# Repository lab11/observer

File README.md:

Observer
========

Observer is an indoor monitoring sensor platform that is optimized to work
with [GAP](https://github.com/lab11/gap).

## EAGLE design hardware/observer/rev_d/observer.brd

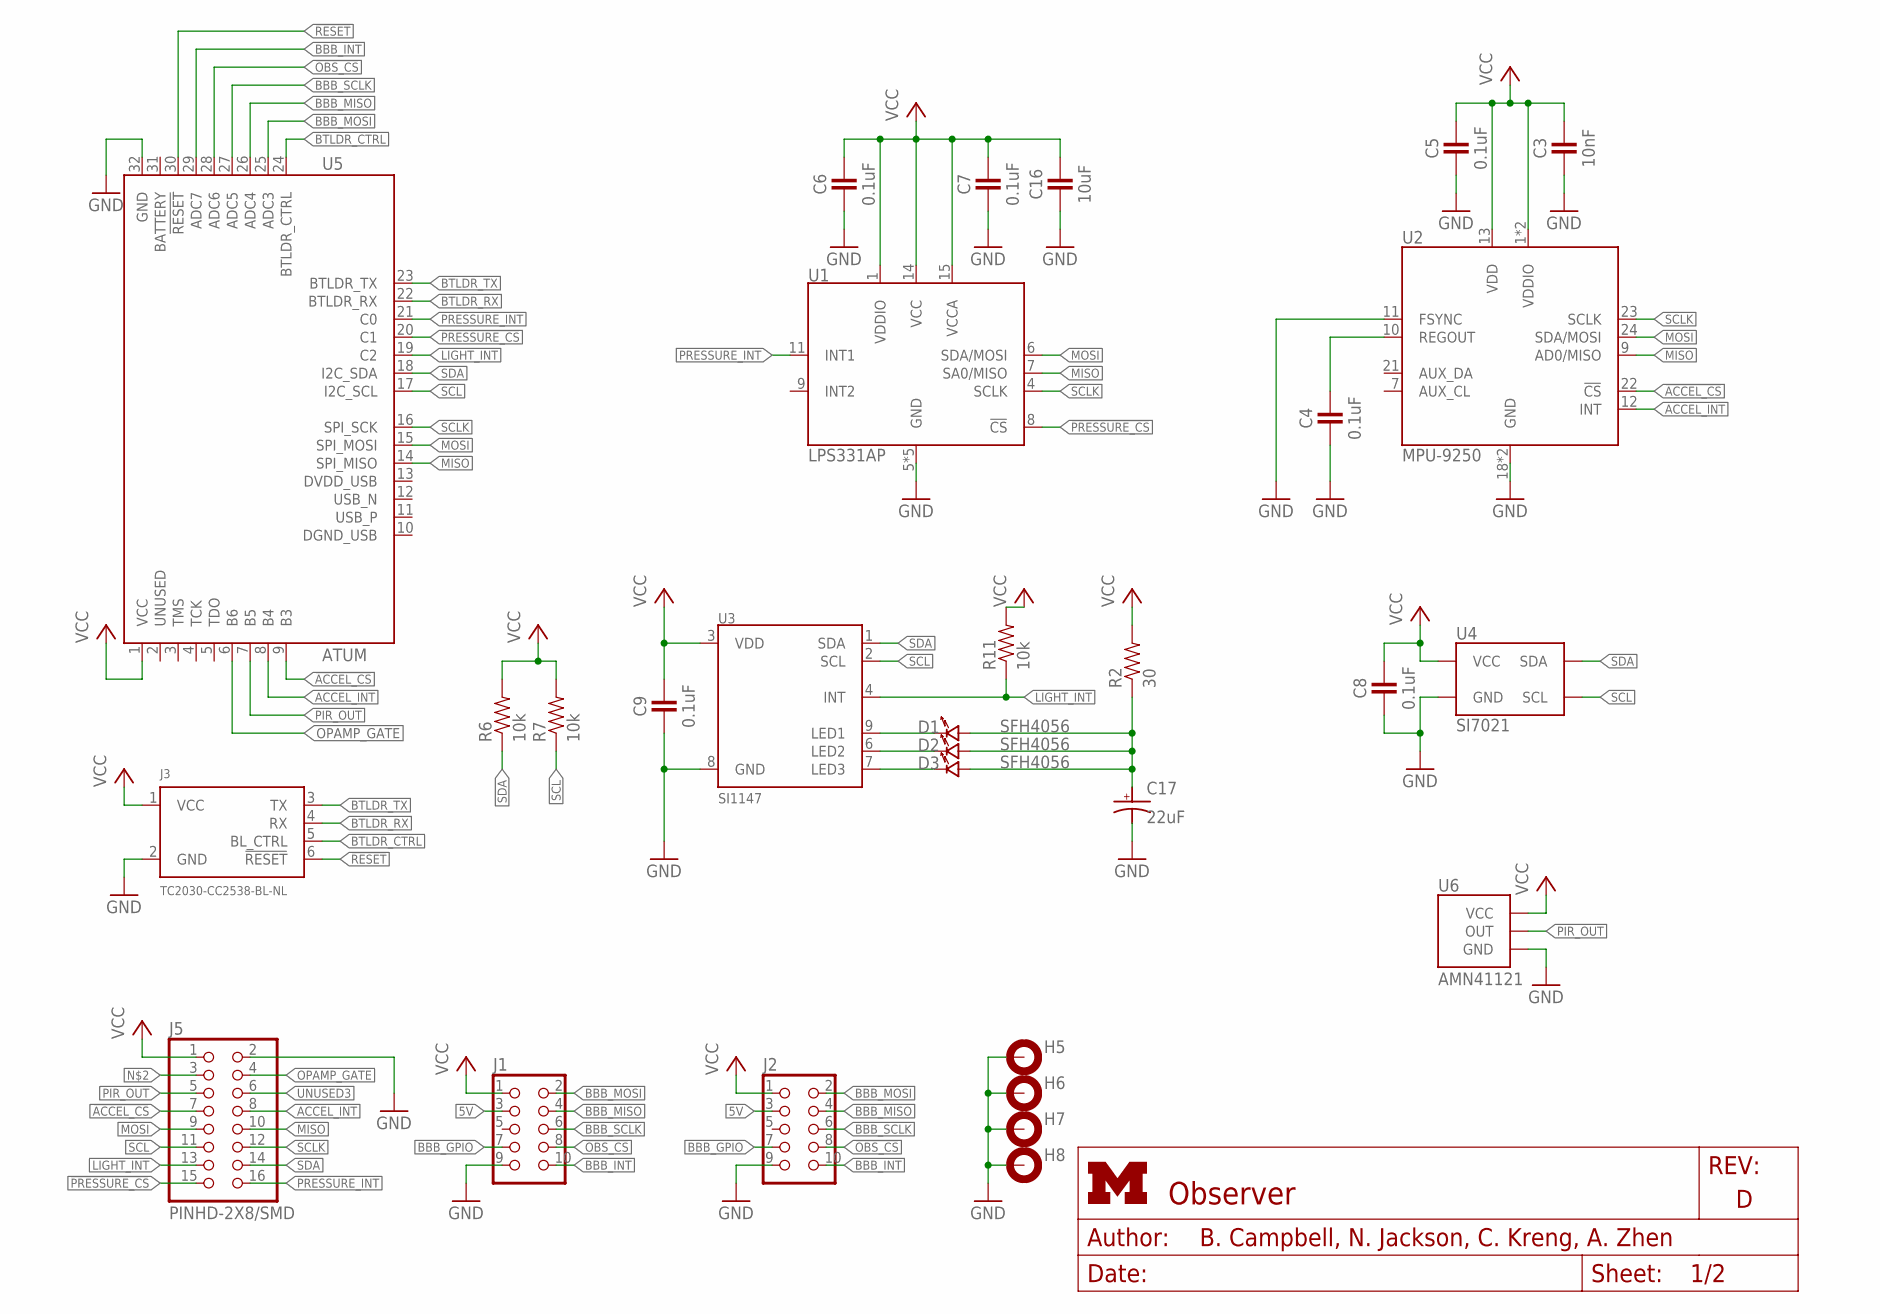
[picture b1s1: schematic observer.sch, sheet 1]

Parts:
C3: 10nF; 0402_CAP; DIGIKEY 490-1312-1-ND
C4, C5, C6, C7, C8, C9: 0.1uF; 0402_CAP; DIGIKEY 490-1318-1-ND
C16: 10uF; 0402_CAP; DIGIKEY 445-8919-1-ND
C17: 22uF; CAP0603; DIGIKEY 511-1493-1-ND
D1, D2, D3: SFH4056
H5, H6, H7, H8: MOUNT-PAD-ROUND3.2; 3,2-PAD
J1, J2: CON_HEADER_2X05-SMD+SHROUDED; PINSHRD_SMT_2X05; DIGIKEY S9185-ND
J3: TC2030-CC2538-BL-NL; TC2030-IDC-NL
J5: PINHD-2X8/SMD; 2X8/SMD
R2: 30; 0402_RES; DIGIKEY RHM30CECT-ND
R6, R7: 10k; 0402_RES; DIGIKEY RHM10.0KCDCT-ND
R11: 10k; 0402_RES; DIGIKEY RHM30CECT-ND
U1: LPS331AP; HCLGA-16/3MM
U2: MPU-9250; QFN-24/3MM
U3: SI1147; QFN-10/2MM
U4: SI7021; DFN-6/3MM
U5: ATUM
U6: AMN41121; AMN2

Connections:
5V: J1.3, J2.3; also elsewhere on the board
!ACCEL_CS: J5.7, U2.22 (!CS), U5.9 (B3)
!OBS_CS: J1.8, J2.8, U5.28 (ADC6); also elsewhere on the board
!PRESSURE_CS: J5.15, U1.8 (!CS), U5.20 (C1)
!RESET: J3.6 (!RESET), U5.30 (!RESET)
ACCEL_INT: J5.8, U2.12 (INT), U5.8 (B4)
BBB_GPIO: J1.7, J2.7; also elsewhere on the board
BBB_INT: J1.10, J2.10, U5.29 (ADC7)
BBB_MISO: J1.4, J2.4, U5.26 (ADC4); also elsewhere on the board
BBB_MOSI: J1.2, J2.2, U5.25 (ADC3); also elsewhere on the board
BBB_SCLK: J1.6, J2.6, U5.27 (ADC5); also elsewhere on the board
BTLDR_CTRL: J3.5 (BL_CTRL), U5.24 (BTLDR_CTRL)
BTLDR_RX: J3.4 (RX), U5.22 (BTLDR_RX)
BTLDR_TX: J3.3 (TX), U5.23 (BTLDR_TX)
GND: C3.2, C4.2, C5.2, C6.2, C7.2, C8.2, C9.2, C16.2, C17.NEG (ANODE), H5.B3,2, H6.B3,2, H7.B3,2, H8.B3,2, J1.9, J2.9, J3.2 (GND), J5.2, U1.5 (GND), U1.10 (GND), U1.12 (GND), U1.13 (GND), U1.16 (GND), U2.11 (FSYNC), U2.18 (GND), U2.20 (GND), U3.8 (GND), U4.2 (GND), U5.32 (GND), U6.GND; also elsewhere on the board
LIGHT_INT: J5.13, R11.1, U3.4 (INT), U5.19 (C2)
MISO: J5.10, U1.7 (SA0/MISO), U2.9 (AD0/MISO), U5.14 (SPI_MISO)
MOSI: J5.9, U1.6 (SDA/MOSI), U2.24 (SDA/MOSI), U5.15 (SPI_MOSI)
unnamed: C4.1, U2.10 (REGOUT)
unnamed: D1.CATHODE, U3.9 (LED1)
unnamed: D2.CATHODE, U3.6 (LED2)
unnamed: D3.CATHODE, U3.7 (LED3)
unnamed: C17.POS (CATHODE), D1.ANODE, D2.ANODE, D3.ANODE, R2.1
OPAMP_GATE: J5.4, U5.6 (B6); also elsewhere on the board
PIR_OUT: J5.5, U5.7 (B5), U6.OUT
PRESSURE_INT: J5.16, U1.11 (INT1), U5.21 (C0)
SCL: J5.11, R7.1, U3.2 (SCL), U4.6 (SCL), U5.17 (I2C_SCL); also elsewhere on the board
SCLK: J5.12, U1.4 (SCLK), U2.23 (SCLK), U5.16 (SPI_SCK)
SDA: J5.14, R6.1, U3.1 (SDA), U4.1 (SDA), U5.18 (I2C_SDA); also elsewhere on the board
UNUSED3: J5.6
VCC: C3.1, C5.1, C6.1, C7.1, C8.1, C9.1, C16.1, J1.1, J2.1, J3.1 (VCC), J5.1, R2.2, R6.2, R7.2, R11.2, U1.1 (VDDIO), U1.14 (VCC), U1.15 (VCCA), U2.1 (VDDIO), U2.8 (VDDIO), U2.13 (VDD), U3.3 (VDD), U4.5 (VCC), U5.1 (VCC), U6.VCC; also elsewhere on the board

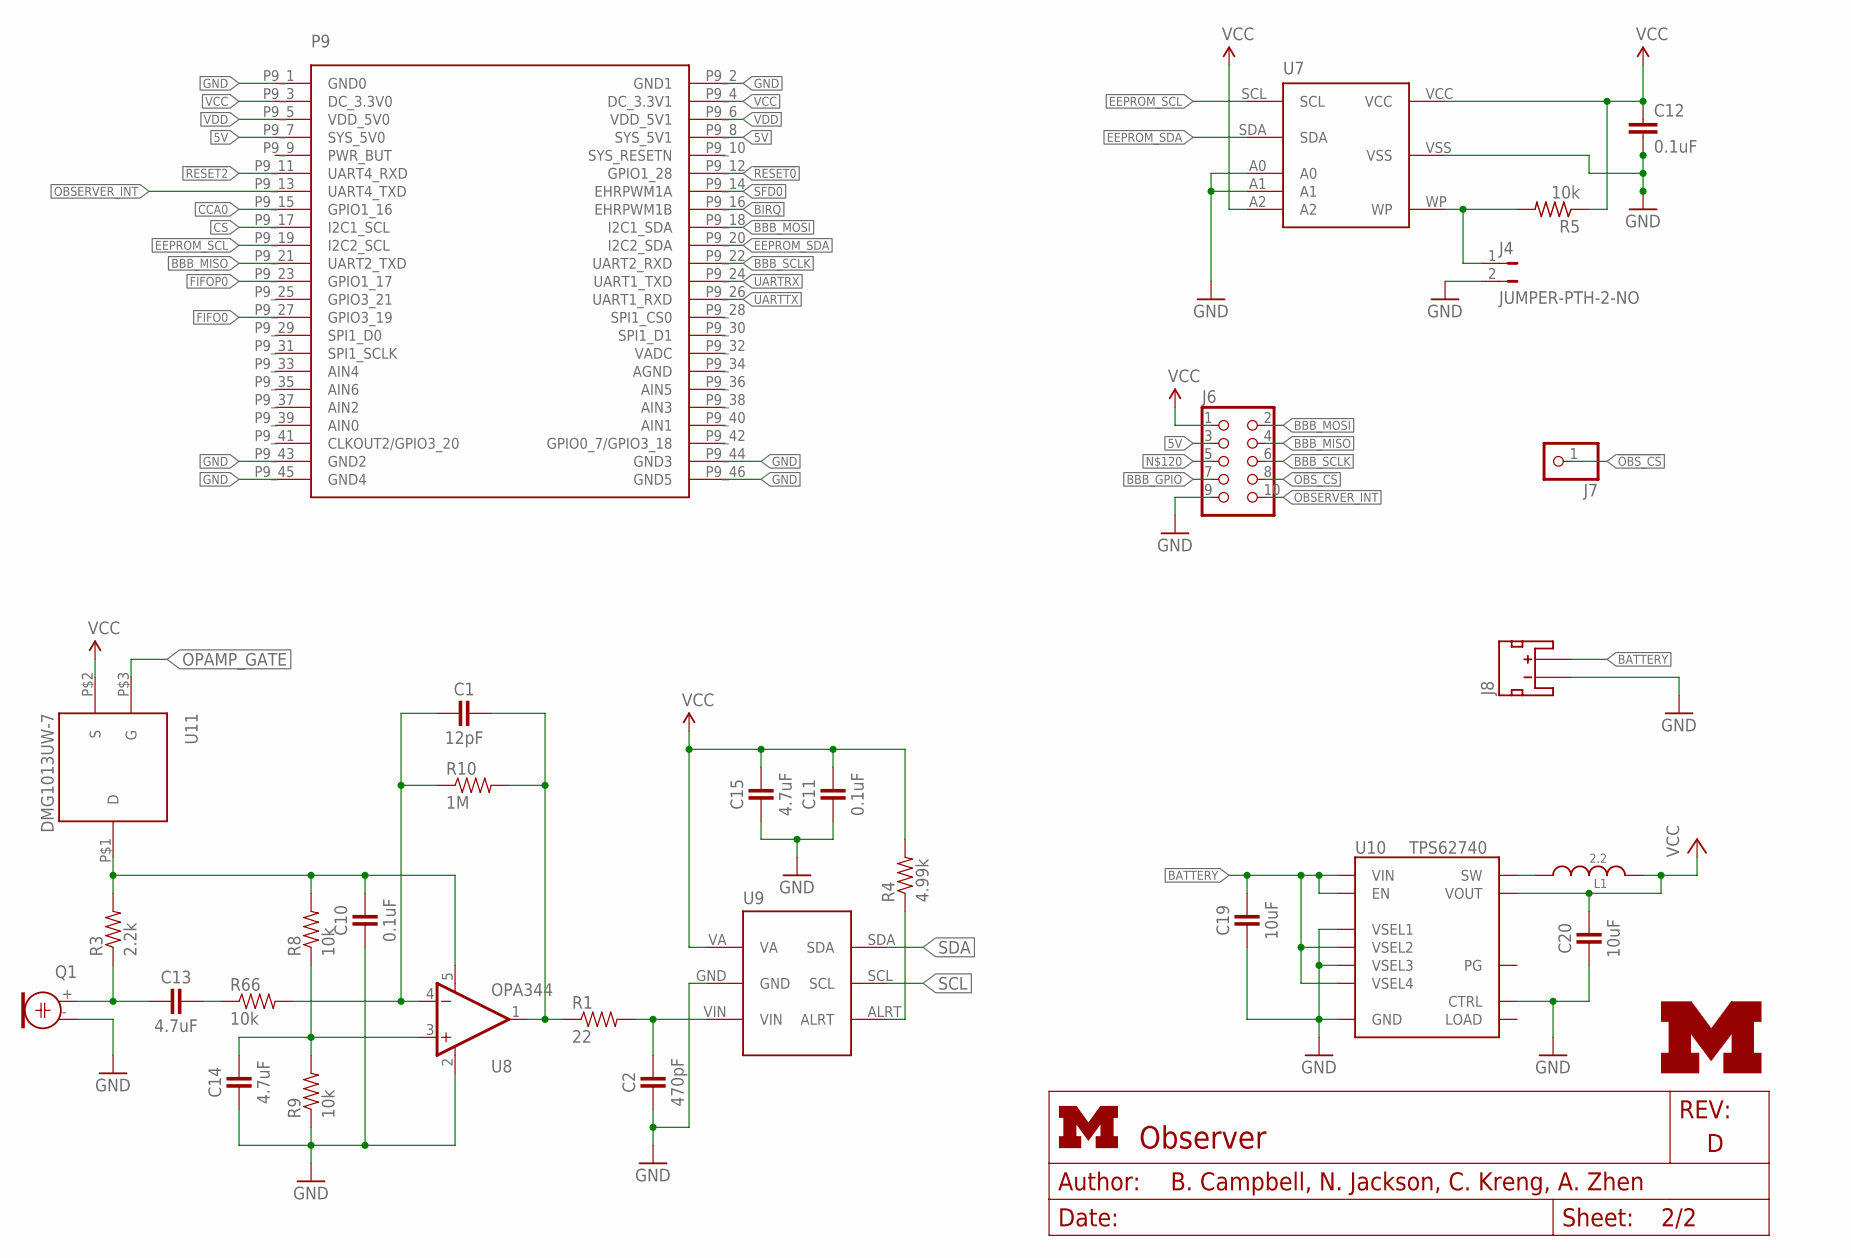
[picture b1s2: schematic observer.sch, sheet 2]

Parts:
C1: 12pF; 0402_CAP
C2: 470pF; 0402_CAP
C10, C11: 0.1uF; 0402_CAP
C12: 0.1uF; C0402; DIGIKEY 490-1318-1-ND
C13, C14, C15: 4.7uF; 0402_CAP
C19, C20: 10uF; 0603_CAP; DIGIKEY 490-7316-1-ND
J4: JUMPER-PTH-2-NO; PTH-JUMPER-2-NO_NO_SILK
J6: CON_HEADER_2X05-PTH+SHROUDED_A; PINSHRD_PTH_2X05
J7: PINHD-1X1; 1X01
J8: JST_2MM_MALE; JST-2-SMD
L1: 2.2; MIPSZ201D
LOGO2: UMICH_SOLID_TINY; UMICH_SOLID_50MIL
P9/P8: BBB_HEADER; BBB_HEADERS
Q1: ELECTRET; ELECTRET_9.7
R1: 22; 0402_RES
R3: 2.2k; 0402_RES
R4: 4.99k; 0402_RES
R5: 10k; R0402; DIGIKEY RHM1.00MCDCT-ND
R8, R9, R66: 10k; 0402_RES
R10: 1M; 0402_RES
U7: CAT24C256WI-GT3
U8: OPA344; SOT23-5
U9: ADC121C021
U10: TPS62740; R-PWSON-12
U11: DMG1013UW-7; SOT-323

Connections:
5V: J6.3, P9/P8.P9_7 (SYS_5V0), P9/P8.P9_8 (SYS_5V1); also elsewhere on the board
!OBS_CS: J6.8, J7.1; also elsewhere on the board
!RESET0: P9/P8.P9_12 (GPIO1_28)
!RESET2: P9/P8.P9_11 (UART4_RXD)
BATTERY: C19.1, J8.2 (+), U10.1 (VIN), U10.8 (VSEL4), U10.10 (VSEL2), U10.12 (EN)
BBB_GPIO: J6.7; also elsewhere on the board
BBB_MISO: J6.4, P9/P8.P9_21 (UART2_TXD); also elsewhere on the board
BBB_MOSI: J6.2, P9/P8.P9_18 (I2C1_SDA); also elsewhere on the board
BBB_SCLK: J6.6, P9/P8.P9_22 (UART2_RXD); also elsewhere on the board
BIRQ: P9/P8.P9_16 (EHRPWM1B)
CCA0: P9/P8.P9_15 (GPIO1_16)
CS: P9/P8.P9_17 (I2C1_SCL)
EEPROM_SCL: P9/P8.P9_19 (I2C2_SCL), U7.SCL
EEPROM_SDA: P9/P8.P9_20 (I2C2_SDA), U7.SDA
FIFO0: P9/P8.P9_27 (GPIO3_19)
FIFOP0: P9/P8.P9_23 (GPIO1_17)
GND: C2.2, C10.2, C11.2, C12.2, C14.2, C15.2, C19.2, C20.2, J4.2, J6.9, J8.1 (-), P9/P8.P9_1 (GND0), P9/P8.P9_2 (GND1), P9/P8.P9_43 (GND2), P9/P8.P9_44 (GND3), P9/P8.P9_45 (GND4), P9/P8.P9_46 (GND5), Q1.- (1), R9.1, U7.A0, U7.A1, U7.VSS, U8.2 (V-), U9.GND, U10.3 (GND), U10.4 (CTRL), U10.9 (VSEL3), U10.11 (VSEL1), U10.NC (GND); also elsewhere on the board
MIC_AIN: C1.1, R1.1, R10.2, U8.1 (OUT)
MIC_INT: R4.1, U9.ALRT
unnamed: C13.2, Q1.+ (2), R3.1
unnamed: C13.1, R66.1
unnamed: C1.2, R10.1, R66.2, U8.4 (-IN)
unnamed: C14.1, R8.1, R9.2, U8.3 (+IN)
unnamed: C2.1, R1.2, U9.VIN
unnamed: L1.1, U10.2 (SW)
unnamed: C10.1, R3.2, R8.2, U8.5 (V+), U11.P$1 (D)
unnamed: J4.1, R5.2, U7.WP
OBSERVER_INT: J6.10, P9/P8.P9_13 (UART4_TXD)
OPAMP_GATE: U11.P$3 (G); also elsewhere on the board
SCL: U9.SCL; also elsewhere on the board
SDA: U9.SDA; also elsewhere on the board
SFD0: P9/P8.P9_14 (EHRPWM1A)
UARTRX: P9/P8.P9_24 (UART1_TXD)
UARTTX: P9/P8.P9_26 (UART1_RXD)
VCC: C11.1, C12.1, C15.1, C20.1, J6.1, L1.2, P9/P8.P9_3 (DC_3.3V0), P9/P8.P9_4 (DC_3.3V1), R4.2, R5.1, U7.A2, U7.VCC, U9.VA, U10.5 (VOUT), U11.P$2 (S); also elsewhere on the board
VDD: P9/P8.P9_5 (VDD_5V0), P9/P8.P9_6 (VDD_5V1)

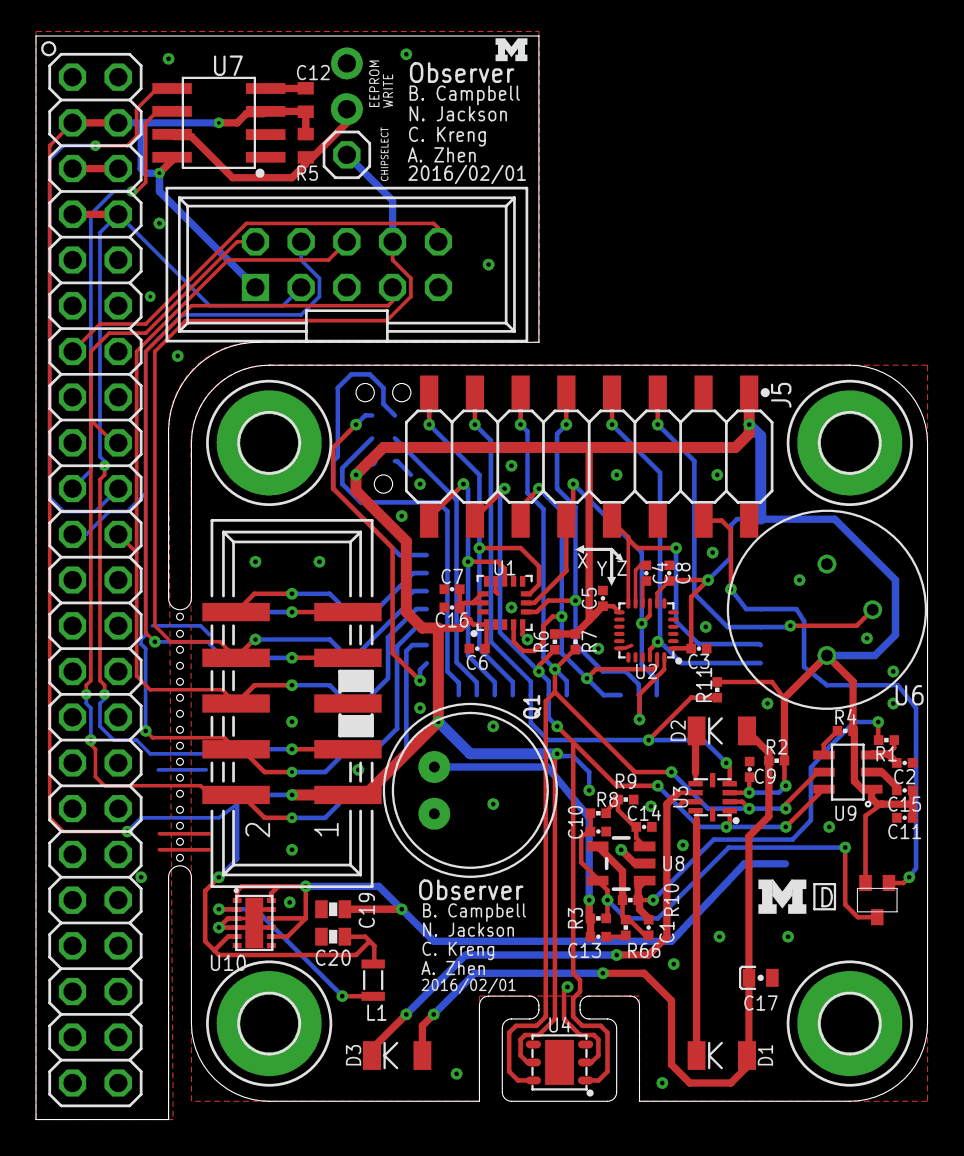
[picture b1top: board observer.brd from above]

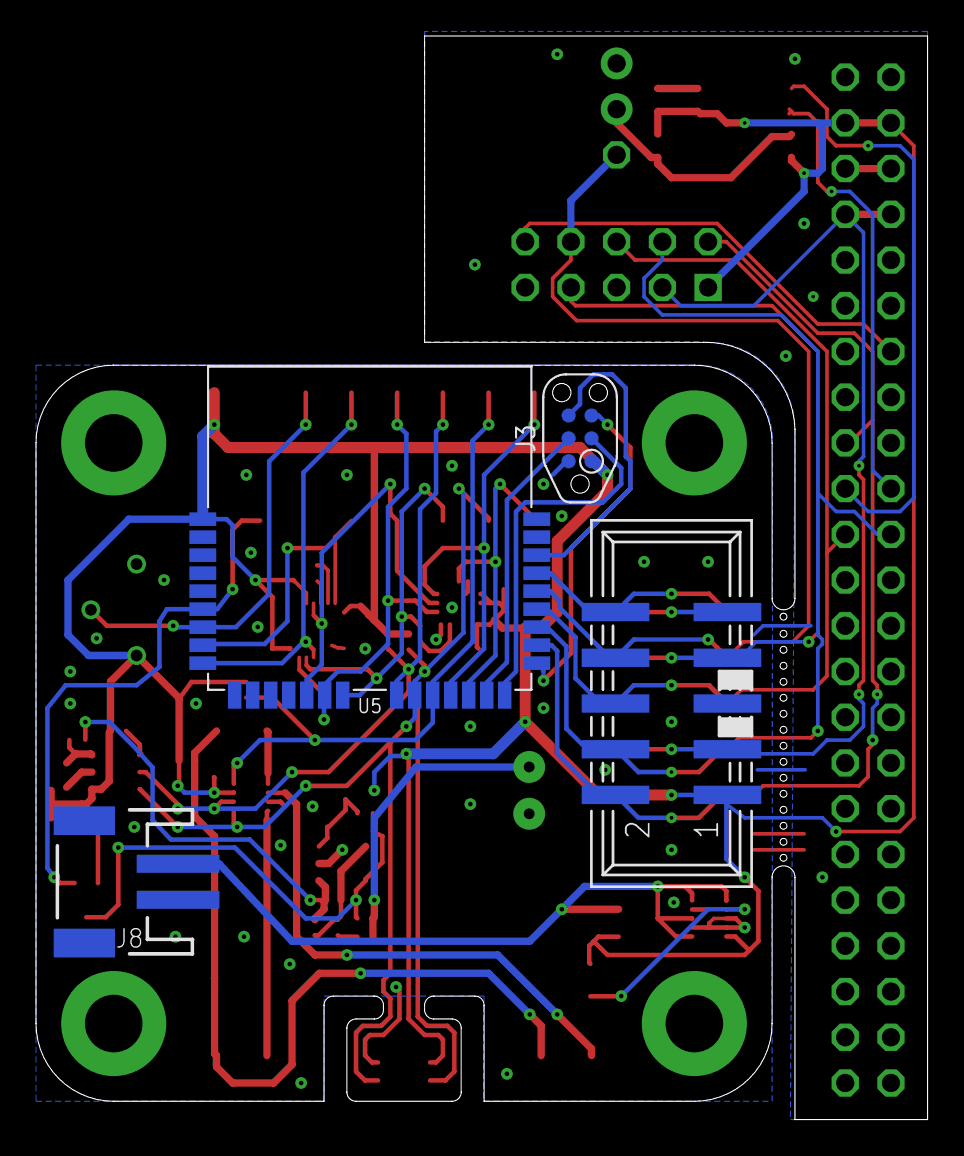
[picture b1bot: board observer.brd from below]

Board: 2 copper layers, 49.5 x 60.2 mm, 62 parts (4 on the bottom side), 45 nets.

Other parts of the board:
U$1: UMICH_SOLID_75MIL
U$2: UMICH_SOLID_50MIL

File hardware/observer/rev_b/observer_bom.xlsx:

Qty | Value | Device | Package | Parts | Description | DIGIKEY
1 | 12pF | CAPACITOR | 0402_CAP | C1 | 0402 Capacitor | 490-6197-1-ND
1 | 470pF | CAPACITOR | 0402_CAP | C2 | 0402 Capacitor | 490-8208-1-ND
1 | 10nF | CAPACITOR | 0402_CAP | C3 | 0402 Capacitor | 490-1312-1-ND
9 | 0.1uF | CAPACITOR | 0402_CAP | C4, C5, C6, C7, C8, C9, C10, C11, C12 | 0402 Capacitor | 490-1318-1-ND
3 | 4.7uF | CAPACITOR | 0402_CAP | C13, C14, C15 | 0402 Capacitor | 490-5915-1-ND
1 | 10uF | CAPACITOR | 0402_CAP | C16 | 0402 Capacitor | 445-8919-1-ND
1 | 22uF | CAP_POL0603 | CAP0603 | C17 | 0603 Capacitor | 511-1493-1-ND
1 | 22 | RESISTOR0402_RES | 0402_RES | R1 | Resistor | RHM22.0CDCT-ND
1 | 30 | RESISTOR0402_RES | 0402_RES | R2 | Resistor | RHM30CECT-ND
1 | 2.2k | RESISTOR0402_RES | 0402_RES | R3 | Resistor | RHM2.2KCECT-ND
1 | 4.99k | RESISTOR0402_RES | 0402_RES | R4 | Resistor | P4.99KLCT-ND
5 | 10k | RESISTOR0402_RES | 0402_RES | R5, R6, R7, R8, R9 | Resistor | RHM1.00MCDCT-ND
1 | 1M | RESISTOR0402_RES | 0402_RES | R10 | Resistor | RHM1.0MCECT-ND
1 | LPS331AP | LPS331AP | HCLGA-16/3MM | U1 | IC PRESSURE SENSOR PIEZO 16HCLGA | 497-12927-1-ND
1 | MPU-9250 | MPU-9250 | QFN-24/3MM | U2 | GYRO/ACCEL/COMPASS/9-AXIS | 1428-1019-1-ND
1 | SI1147 | SI1147 | QFN-10/2MM | U3 | SENSOR DGTL UV INDEX 10QFN | 336-2624-1-ND
1 | SI7021 | SI7021 | DFN-6/3MM | U4 | IC TEMP SENSOR RH 2% DFN | 336-2542-1-ND
1 | ATUM | ATUM | ATUM | U5 | Atum sensorboard prototyping module.
1 | AMN41121 | AMN41121 | AMN2 | U6 | Passive infrared human detection sensor with built-in amp. | 255-2651-ND
1 | CAT24C256WI-GT3 | CAT24C256WI-GT3 | CAT24C256WI-GT3 | U7 | 256kb Serial CMOS EEPROM, organized as 32,768 words of 8 bits each
1 | OPA344 | OPA344 | SOT23-5 | U8 | Single gate rail-to-rail output op-amp. Inputs extend 300mV past rails. | OPA344NACT-ND
1 | ADC121C021 | ADC121C021 | ADC121C021 | U9 | 12 bit 189kHz ADC with alert | ADC121C021CIMK/NOPBCT-ND
1 |  | ELECTRET | ELECTRET_9.7 | Q1 | CMA-4544PF-W Electret microphone | 102-1721-ND
2 | CON_HEADER_2X05-SMD+SHROUDED | CON_HEADER_2X05-SMD+SHROUDED | PINSHRD_SMT_2X05 | J1, J2 | 2x05 pin header | S9185-ND
1 | CON_HEADER_2X05-PTH+SHROUDED_A | CON_HEADER_2X05-PTH+SHROUDED_A | PINSHRD_PTH_2X05 | J6 | 2x05 pin header
1 | PINHD-2X8/SMD | PINHD-2X8/SMD | 2X8/SMD | J5 | 2x08 pin header
1 | TC2030-CC2538-BL-NL | TC2030-CC2538-BL-NL | TC2030-IDC-NL | J3 | Tag connect programmer for the CC2538 bootloader.
4 | MOUNT-PAD-ROUND3.2 | MOUNT-PAD-ROUND3.2 | 3,2-PAD | H5, H6, H7, H8 | MOUNTING PAD, round
1 | BBB_HEADER | BBB_HEADER | BBB_HEADER | P9 | Beaglebone Black P9 Pin Header
3 | SFH4056 | SFH4056 | SFH4056 | D1, D2, D3 | LED IR EMITTER 850NM | 475-3042-1-ND

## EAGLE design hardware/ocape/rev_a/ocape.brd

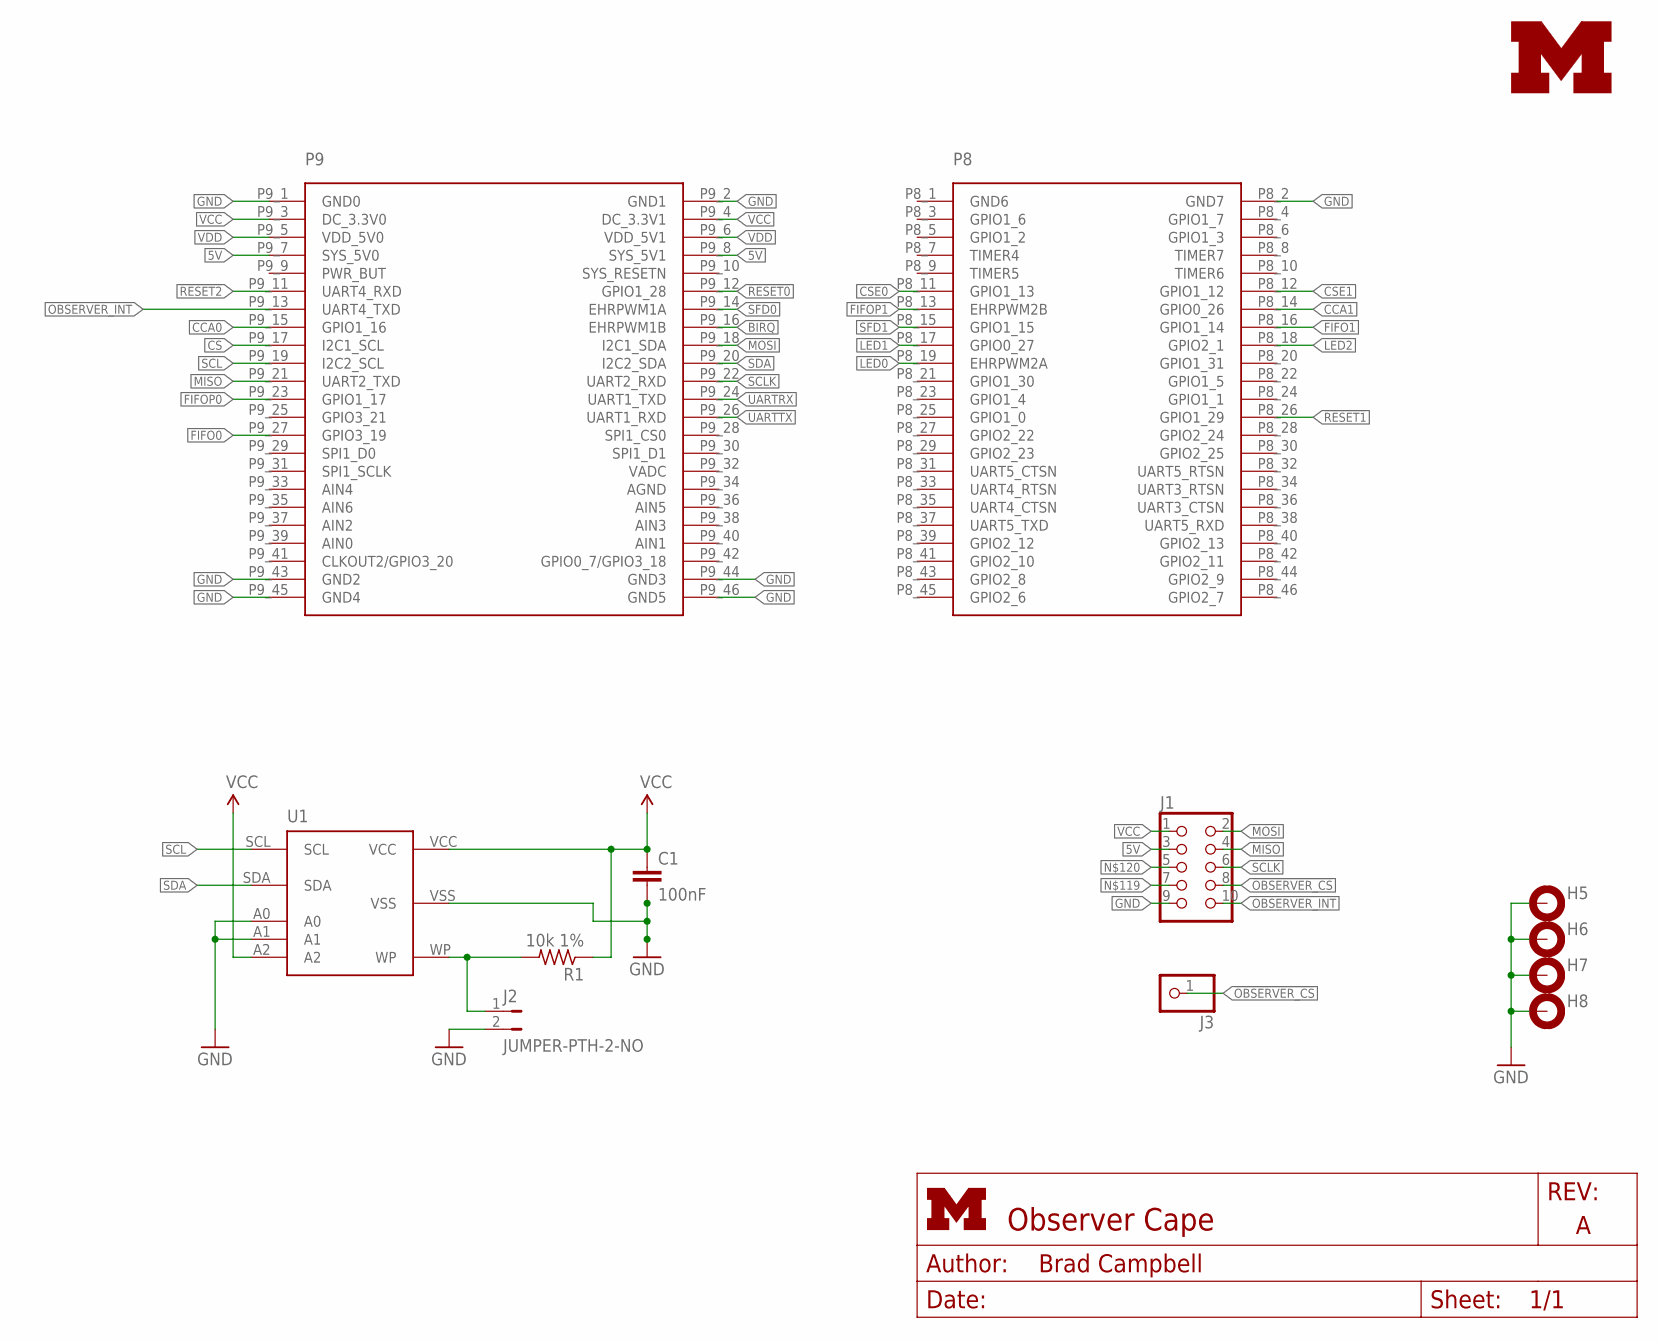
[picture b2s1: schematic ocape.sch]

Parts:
C1: 100nF; C0402; DIGIKEY 490-1318-1-ND
H5, H6, H7, H8: MOUNT-PAD-ROUND3.2; 3,2-PAD
J1: CON_HEADER_2X05-PTH+SHROUDED_A; PINSHRD_PTH_2X05
J2: JUMPER-PTH-2-NO; PTH-JUMPER-2-NO_NO_SILK
J3: PINHD-1X1; 1X01
LOGO1: UMICH_SOLID_SMALL; UMICH_SOLID_75MIL
P9/P8: BBB_HEADERS
R1: 10k 1%; R0402; DIGIKEY RHM1.00MCDCT-ND
U1: CAT24C256WI-GT3

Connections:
5V: J1.3, P9/P8.P9_7 (SYS_5V0), P9/P8.P9_8 (SYS_5V1)
!OBSERVER_CS: J1.8, J3.1
!RESET0: P9/P8.P9_12 (GPIO1_28)
!RESET1: P9/P8.P8_26 (GPIO1_29)
!RESET2: P9/P8.P9_11 (UART4_RXD)
BIRQ: P9/P8.P9_16 (EHRPWM1B)
CCA0: P9/P8.P9_15 (GPIO1_16)
CCA1: P9/P8.P8_14 (GPIO0_26)
CS: P9/P8.P9_17 (I2C1_SCL)
CSE0: P9/P8.P8_11 (GPIO1_13)
CSE1: P9/P8.P8_12 (GPIO1_12)
FIFO0: P9/P8.P9_27 (GPIO3_19)
FIFO1: P9/P8.P8_16 (GPIO1_14)
FIFOP0: P9/P8.P9_23 (GPIO1_17)
FIFOP1: P9/P8.P8_13 (EHRPWM2B)
GND: C1.2, H5.B3,2, H6.B3,2, H7.B3,2, H8.B3,2, J1.9, J2.2, P9/P8.P8_2 (GND7), P9/P8.P9_1 (GND0), P9/P8.P9_2 (GND1), P9/P8.P9_43 (GND2), P9/P8.P9_44 (GND3), P9/P8.P9_45 (GND4), P9/P8.P9_46 (GND5), U1.A0, U1.A1, U1.VSS
LED0: P9/P8.P8_19 (EHRPWM2A)
LED1: P9/P8.P8_17 (GPIO0_27)
LED2: P9/P8.P8_18 (GPIO2_1)
MISO: J1.4, P9/P8.P9_21 (UART2_TXD)
MOSI: J1.2, P9/P8.P9_18 (I2C1_SDA)
unnamed: J2.1, R1.2, U1.WP
OBSERVER_INT: J1.10, P9/P8.P9_13 (UART4_TXD)
SCL: P9/P8.P9_19 (I2C2_SCL), U1.SCL
SCLK: J1.6, P9/P8.P9_22 (UART2_RXD)
SDA: P9/P8.P9_20 (I2C2_SDA), U1.SDA
SFD0: P9/P8.P9_14 (EHRPWM1A)
SFD1: P9/P8.P8_15 (GPIO1_15)
UARTRX: P9/P8.P9_24 (UART1_TXD)
UARTTX: P9/P8.P9_26 (UART1_RXD)
VCC: C1.1, J1.1, P9/P8.P9_3 (DC_3.3V0), P9/P8.P9_4 (DC_3.3V1), R1.1, U1.A2, U1.VCC
VDD: P9/P8.P9_5 (VDD_5V0), P9/P8.P9_6 (VDD_5V1)

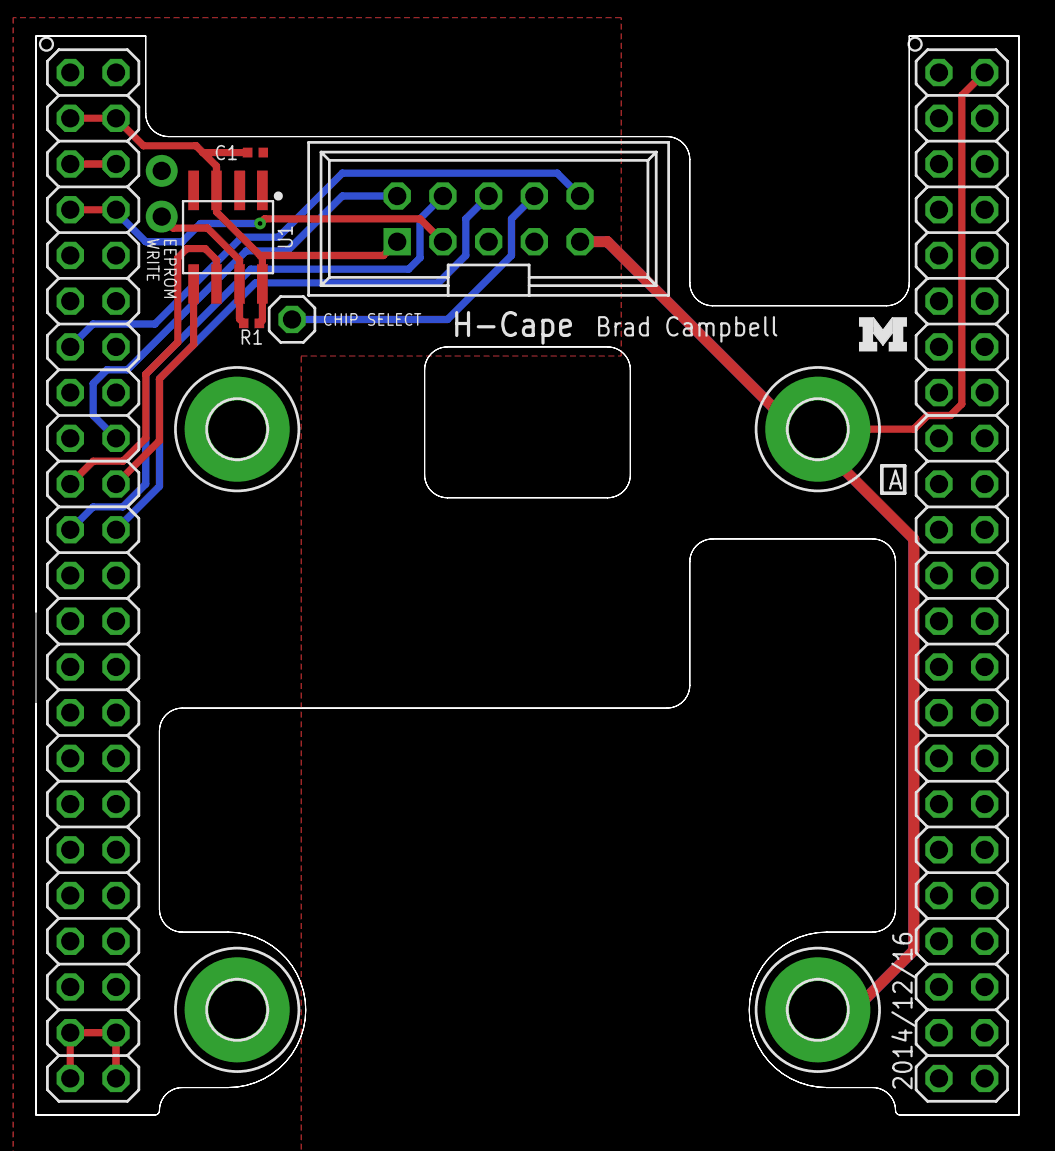
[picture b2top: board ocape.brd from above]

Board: 4 copper layers, 54.6 x 59.9 mm, 12 parts (0 on the bottom side), 12 nets.

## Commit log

2015-03-23 Added atum and contiki submodules
2015-03-24 Revert "Initial commit" Submodules are a stupid idea This reverts commit 1fd872b0bbc6876e9a30ed0d911b9573ee2626ab.
2015-03-24 Revert "Added atum and contiki submodules" Submodules are a stupid idea This reverts commit b7c9c013c6916bf5aa85a08452e0f45e0531b0ad.
2015-03-24 readded README
2015-03-26 Added source and headers for atum with contiki
2015-03-26 Added spi_example process
2015-03-26 revert blink.c to normal
2015-03-27 first attempt at duplex read/write
2015-03-27 abandoned trying to get duplex read/write
2015-03-28 started driver for pressure (lps331ap)
2015-03-28 added mpu9150 as an example and starting files for si7021
2015-03-28 added register addresses
2015-03-28 turn on sensor and poll who am i
2015-03-29 added mpu9250, started header file with registers
2015-03-30 si1147 initial commit
2015-03-30 fixed read function SPI CS timing
2015-03-30 Working reads from the pressure sensor
2015-03-31 Renamed read/write, restructured ctrl_reg1 struct
2015-03-31 si1147: cleaned up autoincrement disable
2015-03-31 si1147: cleaned up mode/meas rate in si1147_init
2015-03-31 si1147: added debug statements
2015-03-31 added more configuration defines
2015-03-31 Si7021 initial commit
2015-03-31 Started implementing irq handler for pressure
2015-04-02 added rev a files
2015-04-02 si1147: clean up slave address stuff
2015-04-02 si1147: general cleanup
2015-04-02 si1147: read/write parameter functions
2015-04-02 si1147: added ALS measurements
2015-04-02 si1147: massive header file cleanup
2015-04-03 added additional function for Si7021
2015-04-04 Added reva hcape
2015-04-05 added schematic for the microphone
2015-04-05 added library for microphone
2015-04-05 Added single p9 header for BBB
2015-04-05 Updated bbb header device
2015-04-05 Started observer rev b
2015-04-05 can make blink with uknoblic/contiki SSI1 support
2015-04-06 ssi1 definitions
2015-04-06 got ssi1 to work master, trying to configure it as slave, so far unsucessful
2015-04-06 started routing
2015-04-06 added in the ADC
2015-04-06 Finished routing header signals, need to add mousebites and microphone hardware
2015-04-07 added mic and opamp to sch
2015-04-07 added mousebites
2015-04-07 small change to mousebites
2015-04-07 updated ADC
2015-04-07 changed from ADC1210C027 to ADC1210C021
2015-04-07 Finished routing, needs to be looked over for correctness
2015-04-07 Removed empty adafruit folder
2015-04-07 Fixed header on motherboard, added decoupling cap for op amp
2015-04-07 fixed some spacing issues
2015-04-07 Fixed clearance issues near BBB header and mousebites
2015-04-07 started bom, need to rename caps/res in order of increasing value
2015-04-07 added excel sheet, need to rename passives
2015-04-07 Renamed passives in order of increasing value, highlighted parts needed in bom
2015-04-07 added all missing digikey part numbers new parts highlighted in orange
2015-04-08 Shipped off board, fixed DRU errors.
2015-04-13 testing spi for mpu9250
2015-04-13 Removed timers from accelerometer, works
2015-04-14 have int working
2015-04-14 cleaned up int defines
2015-04-15 si1147: disable watchdog timer
2015-04-15 si1147: can do forced mode, working on interrupts
2015-04-15 observer-main: create main process
2015-04-16 si1147: modified ADC params
2015-04-16 observer-main: using etimer
2015-04-16 mpu9250: cleaned up to fit in with main
2015-04-16 mpu9250: in main dir fixed a the startup time
2015-04-16 observer-main: integrated mpu925 but no promises
2015-04-17 observer-main: mpu9250 and si1147 getting reads
2015-04-17 Sensor reading correct data
2015-04-17 adc121c021: successive write/reads not working
2015-04-18 gave up on stupid SPI reads, should give accurate reads
2015-04-18 misc: added miscellaneous functions
2015-04-18 mpu9250: clear sleep bit at beginning of init
2015-04-18 observer-main lps331ap files
2015-04-18 si1147: using misc functions
2015-04-18 observer-main: pressure/accel don't work together
2015-04-19 Changed to use iterating reads/writes and utilizing SPI flush LPS331AP now reports correct readings
2015-04-19 Moved driver source for lps331ap to contiki/dev
2015-04-19 Moved drivers to /dev and updated main process
2015-04-19 Added spi flush to mpu9250
2015-04-19 amn41122: added to dev... everything working
2015-04-20 standardized printing
2015-04-20 si7021: added back in Cynthia's code. slightly modified
2015-04-20 observer-main: working with all sensors but the microphone
2015-04-20 observer-main: now getting the raw stuff
2015-04-20 Cynthia's adc code that was on yorkpatty
2015-04-20 ADC working and added to the main process
2015-04-20 added checksum
2015-04-20 continued checksum
2015-04-20 included the files for networking, modified project-conf to include networking code
2015-04-20 not sure why mpu9250 was not in master, adding the old, working version
2015-04-20 main can poll sensors for data and send packets to beaglebone
2015-04-20 source file for polling 15.4 and parsing data to stdout, python script for demo using stdin as input
2015-04-21 changed ADC
2015-04-21 fixed adc hang
2015-04-21 changed adc algorithm
2015-05-21 added interrupts for mpu9250, revised isr: disables interrupts, polls main process, main process responsible for enabling interrups before sleeping (this done to provide atomicity)
2015-05-21 forgot to commit actual drivers in last commit: amn41122 and mpu9250
2015-05-27 old source/makefiles do not work with current version of contiki; updated for support
2015-06-19 forgot to initialize spi
2015-06-25 observer rev_c
2015-06-25 observer low power tests
2015-06-25 observer rev_c zip to fab
2015-06-29 connected opamp gate signal to header for debugging
2015-06-29 updated zip to fab for the revised board
2015-06-30 lps331ap oneshot working, removed old board zip to fabs
2015-07-22 switched from using rtimer to vtimer for periodic wakeup
2015-07-22 changed lps331ap init to enable one-shot mode, not continuous sampling
2015-07-23 power-up int accel, broke stuff :shit:
2015-08-11 lots of changes for observer_lp (i don't commit often)
2015-08-11 observer_coap app
2015-08-11 actually reverting changes for coap, stupid git...
2015-08-12 left some makefiles out accidentally
2015-08-17 motion detected timeout added (using etimer, not rtc b/c spi conflict)
2015-08-18 everything seems to work fine....
2015-08-20 reduced ram size (just set a :shit: ton of uip macros to 0) seems to not break my stuff so... ok
2015-08-20 power-up interrupts return with interrupts disabled, main process restores interrupts so that peripherals aren't interrupted when reading and transmitting is atomic
2015-08-21 :v: minus :point_up: = Ha, f you
2015-08-22 seems to work?
2015-08-26 moved callbacks to main process source file; generalized interrupt enable functions for pir and rtc
2015-08-26 changed flag check from led to global variable
2015-08-27 blink for lp testing
2015-08-27 added crc check for temp/humid sensor
2015-08-27 led toggle on motion
2015-08-27 forgot to disable interrupts in pir handler
2015-08-28 changed callback to include arguments, probably won't fix the problem
2015-08-28 blink: test for powerup int enable
2015-08-29 changes....
2015-08-29 web demo shit
2015-08-30 board testing
2015-08-31 GAP read and post scripts
2015-09-03 isues
2015-09-03 overhauled event processing, might break? currently deployed and testing
2015-09-03 changed demo to extract time from the packet, GATD deduplicator still can't filter correctly
2015-09-04 check CRC
2015-11-23 no more atum readme
2016-01-24 kmods
2016-01-24 post
2016-01-27 reliable lpm2 entry; reliable broadcast
2016-01-30 accel power up int; press oneshot; still need gpio for lowpower
2016-01-31 still drawing 3mA; can't pinpoint where
2016-02-01 stupid no pullup; order uA draw with external pullup
2016-02-01 added light int pullup; connected amp to pfet drain; voltage regulator output 2.8V;
2016-02-01 rev_d gerbers
2016-02-01 deleted temp board files
2016-02-02 zip files for fab of rev_d
2016-02-02 test apps for accel and press
2016-02-24 ak8963 tests
2016-03-10 can go to sleep with rtimer and wake up, all in LPM2
2016-03-21 incremental low power updates
2016-03-22 more incremental power changes/correct pin assignments
2016-03-22 still functioning, didn't break
2016-03-22 fixed spi/rtc working in lpm with rtimer
2016-03-22 reduced process thread size/no names
2016-03-22 clear int before enable alarm, just in case
2016-03-22 mpu9250 no low clock; lps331ap no float mosi; rtc uses low clock so must come first
2016-03-23 mpu must be last spi before sleep for some reason; maybe hanging/idling when other spi transactions occur? b/c changing spi mode doesn't fix nor lps as last spi (which uses same spi mode)
2016-03-23 mpu latch in separate process works; mpu must be last spi possibly b/c of shared I2C lines putting it into weird state when other spi trans occurs but can't disable I2C b/c need magnetometer
2016-03-23 lpm working with all periphs on board;can't figure out how to change mpu mode to read magnetometer
2016-03-23 can sample all periphs and broadcast; seems to return to low power state
2016-03-23 working without accel int (but still need to set pin up for input, or else floating
2016-03-24 still functioning, not out of ram retained yet
2016-03-24 pir backoff, rtimer and process for handling event
2016-03-24 increase tx power
2016-03-24 fixed interrupt firing when re-enabling wake-up interrupt
2016-03-24 fixed mpu mystery drain, i2c shared with spi lines so unless mpu was last spi transmission, it would think it got i2c trans and get into weird state
2016-03-25 update mpu interrupt config; using RMW for enabling i2c master on mpu; can communicate with ak8963, just need to disable i2c master on mpu before sleeping
2016-03-25 must disable I2C master before sleeping; need to disable cycling then wait at most(?) 10ms before reconfiguring mpu to do other things like enabling I2C master, must disable I2C master and reenable c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
2016-03-29 added mag data to broadcast, including raw data and factory offsets; to be computed on server side b/c floating point
2016-03-29 real mag data and accel data
2016-03-29 update parsing and post
2016-03-29 pir process also includes mag and accel
2016-04-05 moved pir rtimer to interrupt handler to keep atomic; moved pir int enable after busy loop to avoid getting into weird state at start
2016-04-05 forgot to push Makefile changes
2016-04-05 visuals/charts and stuff
2016-04-05 put dependent libraries in repo; change html src to point to these
2016-04-05 add Chart.Scatter library as submodule
2016-04-05 busted submodule, removing and readding later
2016-04-05 readded Chart.js v2 library as submodule
2016-04-06 updated library src to submodule
2016-04-20 spi slave on ssi1 working
2016-04-20 spiSlave driver adapted from yesheng's
2016-04-20 changed spi clock divider

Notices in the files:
parts and their libraries:
SparkFun-Passives: Licensing: CC v3.0 Share-Alike You are welcome to use this library for commercial purposes.
SparkFun-Aesthetics: Licensing: Creative Commons ShareAlike 4.0 International - https://creativecommons.org/licenses/by-sa/4.0
